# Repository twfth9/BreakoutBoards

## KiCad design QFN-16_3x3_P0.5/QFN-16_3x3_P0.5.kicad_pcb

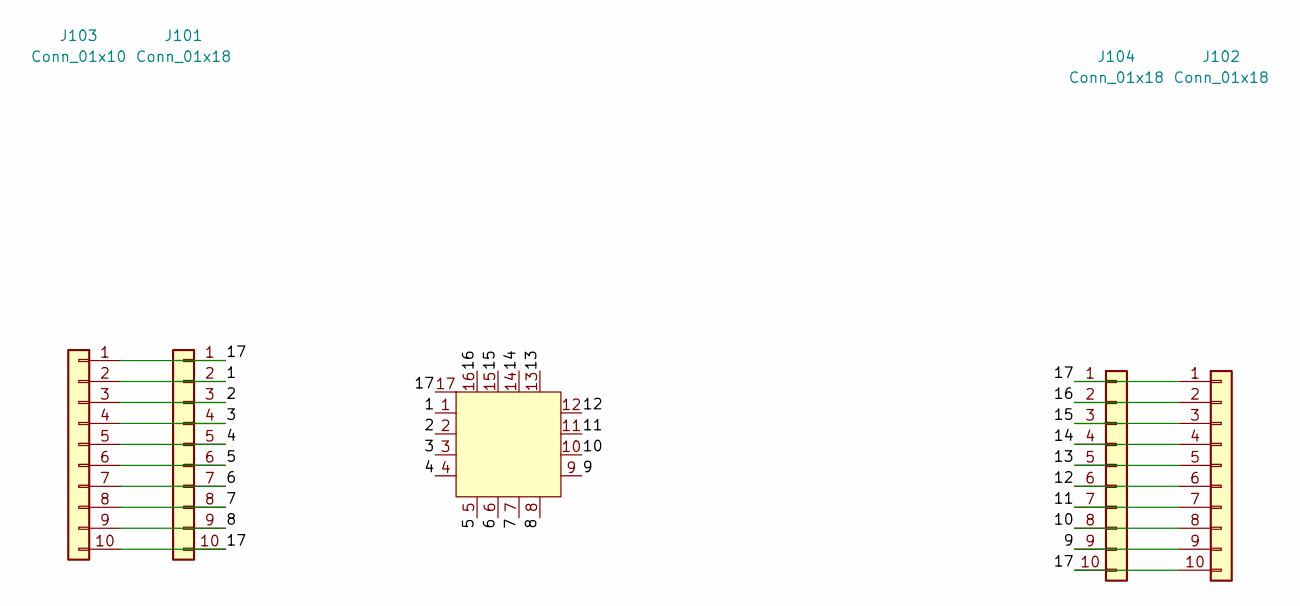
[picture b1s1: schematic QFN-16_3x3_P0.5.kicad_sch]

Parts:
J101: Conn_01x18; PinHeader_1x10_P2.54mm_Vertical_SMD_Pin1Left
J102: Conn_01x18; PinHeader_1x10_P2.54mm_Vertical
J103: Conn_01x10; PinHeader_1x10_P2.54mm_Vertical
J104: Conn_01x18; PinHeader_1x10_P2.54mm_Vertical_SMD_Pin1Right
U101: QFN-16; QFN-16-1EP_3x3mm_P0.5mm_EP1.7x1.7mm_ThermalVias

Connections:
/1: J101.2, J103.2, U101.1
/2: J101.3, J103.3, U101.2
/3: J101.4, J103.4, U101.3
/4: J101.5, J103.5, U101.4
/5: J101.6, J103.6, U101.5
/6: J101.7, J103.7, U101.6
/7: J101.8, J103.8, U101.7
/8: J101.9, J103.9, U101.8
/9: J102.9, J104.9, U101.9
/10: J102.8, J104.8, U101.10
/11: J102.7, J104.7, U101.11
/12: J102.6, J104.6, U101.12
/13: J102.5, J104.5, U101.13
/14: J102.4, J104.4, U101.14
/15: J102.3, J104.3, U101.15
/16: J102.2, J104.2, U101.16
/17: J101.1, J101.10, J102.1, J102.10, J103.1, J103.10, J104.1, J104.10, U101.17

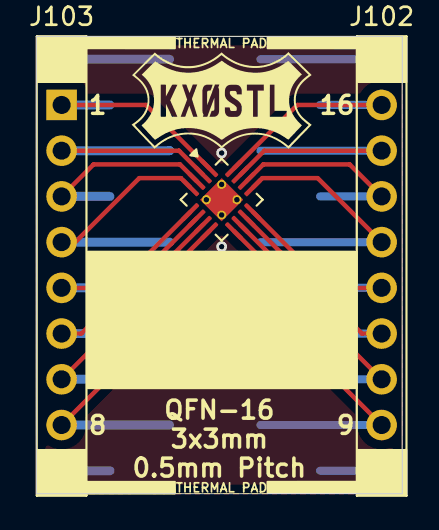
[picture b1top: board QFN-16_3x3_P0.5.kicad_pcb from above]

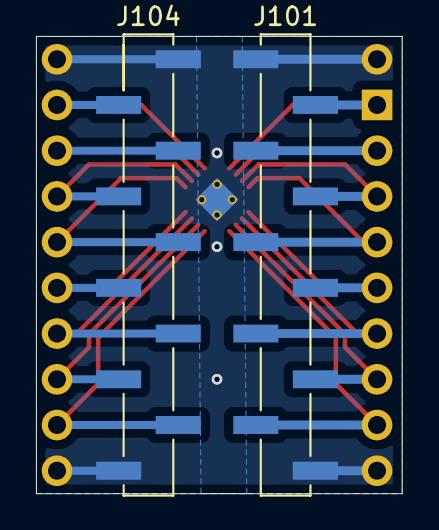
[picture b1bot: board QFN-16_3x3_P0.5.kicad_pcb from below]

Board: 2 copper layers, 20.3 x 25.4 mm, 5 parts (2 on the bottom side), 17 nets.

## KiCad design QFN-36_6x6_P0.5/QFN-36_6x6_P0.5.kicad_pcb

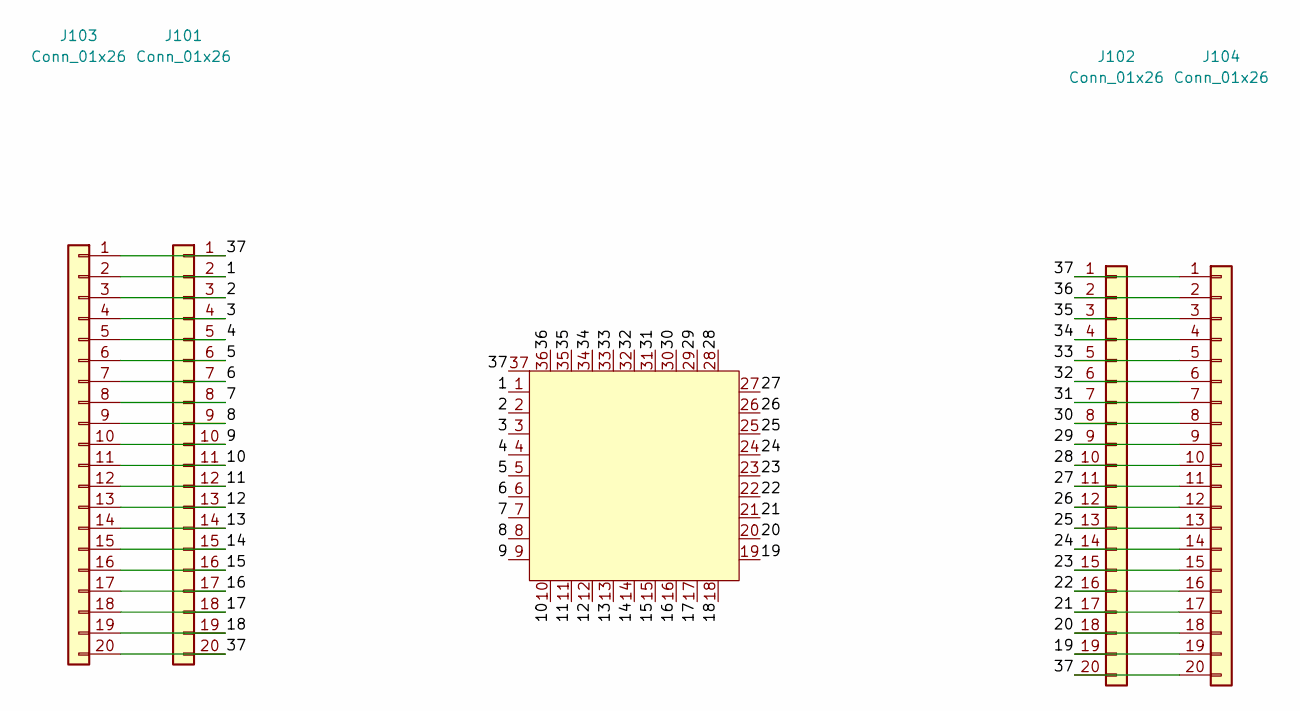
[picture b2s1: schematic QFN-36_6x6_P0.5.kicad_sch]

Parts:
J101, J102: Conn_01x26; PinHeader_1x20_P2.54mm_Vertical
J103: Conn_01x26; PinHeader_1x20_P2.54mm_Vertical_SMD_Pin1Left
J104: Conn_01x26; PinHeader_1x20_P2.54mm_Vertical_SMD_Pin1Right
U101: QFN-48; QFN-36-1EP_6x6mm_P0.5mm_EP3.7x3.7mm_ThermalVias

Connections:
/1: J101.2, J103.2, U101.1
/2: J101.3, J103.3, U101.2
/3: J101.4, J103.4, U101.3
/4: J101.5, J103.5, U101.4
/5: J101.6, J103.6, U101.5
/6: J101.7, J103.7, U101.6
/7: J101.8, J103.8, U101.7
/8: J101.9, J103.9, U101.8
/9: J101.10, J103.10, U101.9
/10: J101.11, J103.11, U101.10
/11: J101.12, J103.12, U101.11
/12: J101.13, J103.13, U101.12
/13: J101.14, J103.14, U101.13
/14: J101.15, J103.15, U101.14
/15: J101.16, J103.16, U101.15
/16: J101.17, J103.17, U101.16
/17: J101.18, J103.18, U101.17
/18: J101.19, J103.19, U101.18
/19: J102.19, J104.19, U101.19
/20: J102.18, J104.18, U101.20
/21: J102.17, J104.17, U101.21
/22: J102.16, J104.16, U101.22
/23: J102.15, J104.15, U101.23
/24: J102.14, J104.14, U101.24
/25: J102.13, J104.13, U101.25
/26: J102.12, J104.12, U101.26
/27: J102.11, J104.11, U101.27
/28: J102.10, J104.10, U101.28
/29: J102.9, J104.9, U101.29
/30: J102.8, J104.8, U101.30
/31: J102.7, J104.7, U101.31
/32: J102.6, J104.6, U101.32
/33: J102.5, J104.5, U101.33
/34: J102.4, J104.4, U101.34
/35: J102.3, J104.3, U101.35
/36: J102.2, J104.2, U101.36
/37: J101.1, J101.20, J102.1, J102.20, J103.1, J103.20, J104.1, J104.20, U101.37

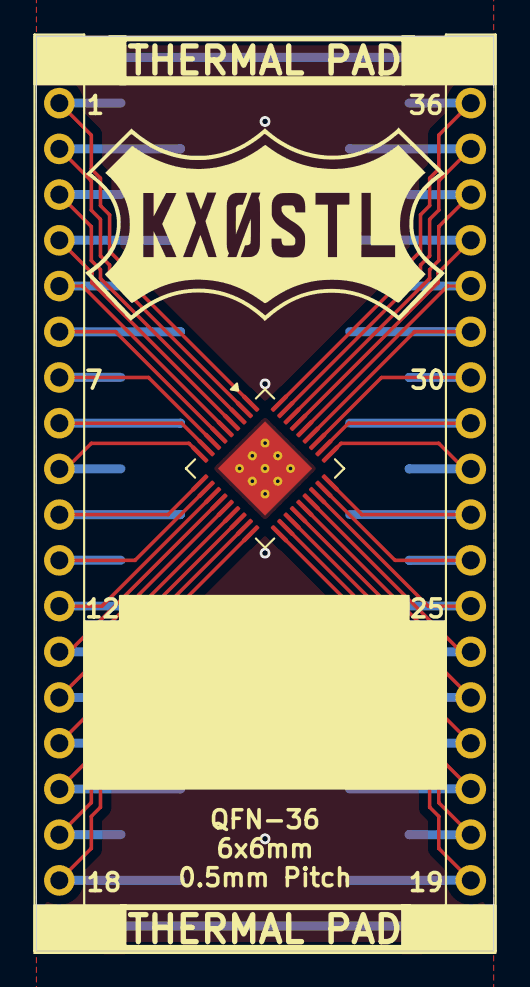
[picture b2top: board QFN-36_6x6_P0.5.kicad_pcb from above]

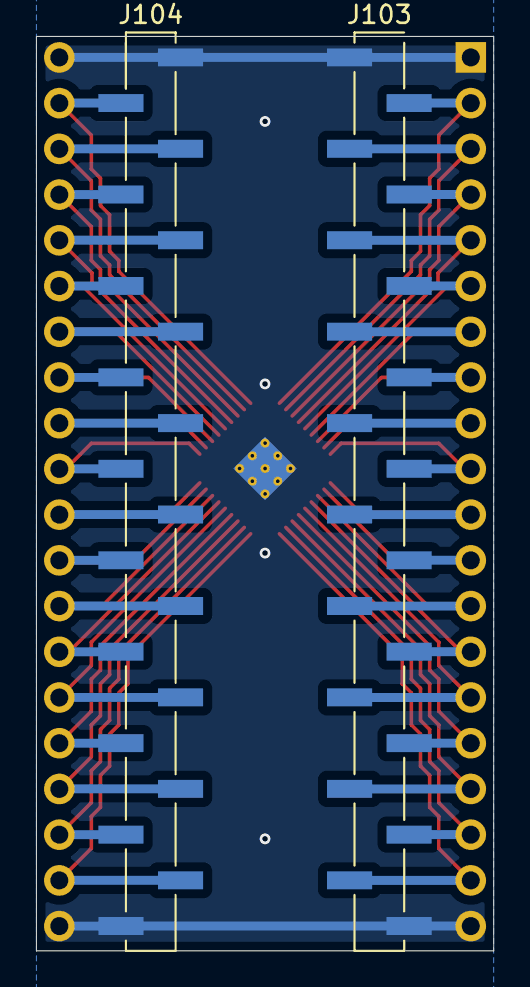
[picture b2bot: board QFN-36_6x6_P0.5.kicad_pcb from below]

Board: 2 copper layers, 25.4 x 50.8 mm, 5 parts (2 on the bottom side), 37 nets.
